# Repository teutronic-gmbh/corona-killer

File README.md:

# Corona-Killer

Luftsterilisation mittels UV-Licht

entworfen für den Einsatz in Klassenräumen im Winterhalbjahr 2020/2021

die eingebaute CO2-Messung erkennt die Anwesenheit von Schülern und schaltet die Luftsterilisation ein

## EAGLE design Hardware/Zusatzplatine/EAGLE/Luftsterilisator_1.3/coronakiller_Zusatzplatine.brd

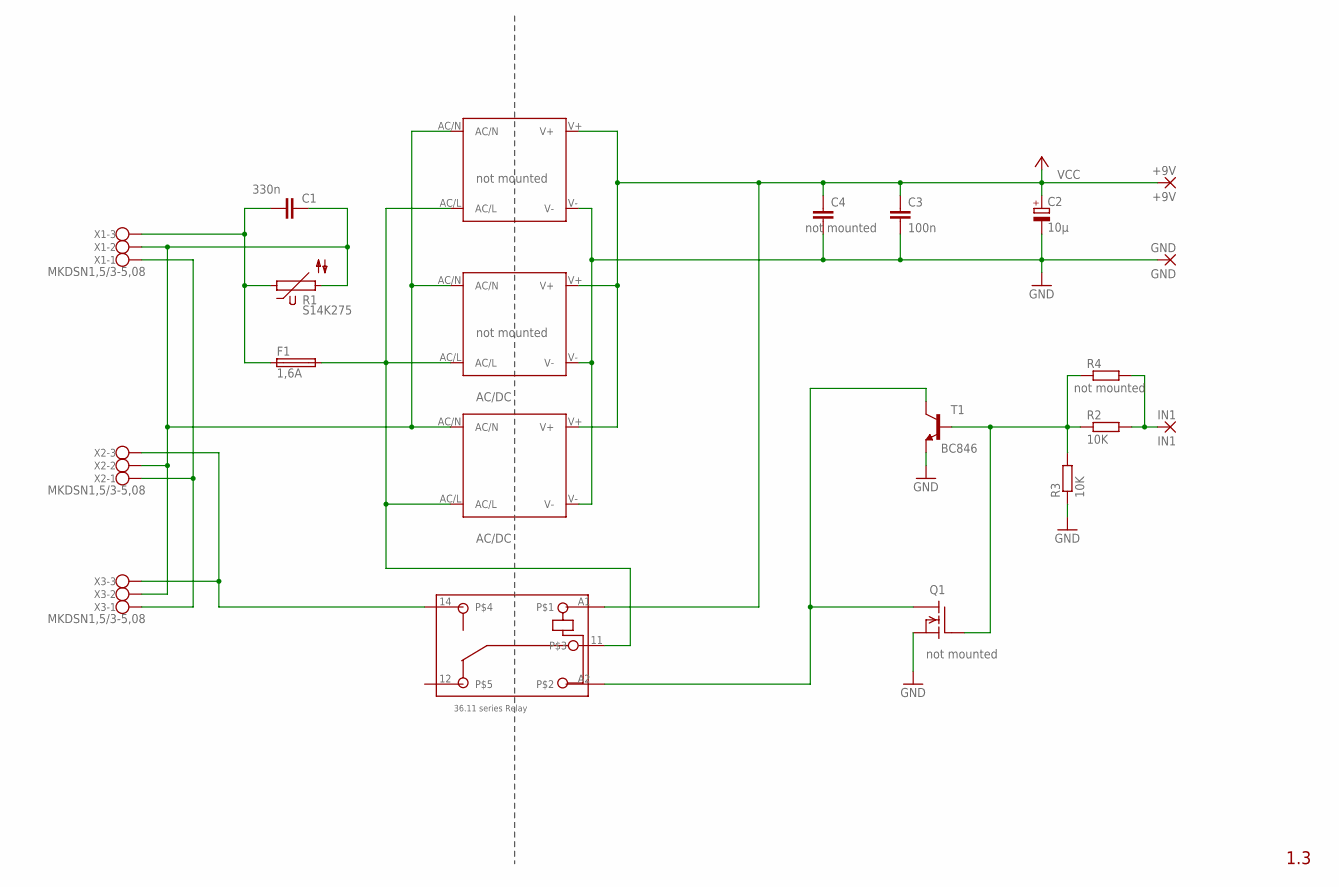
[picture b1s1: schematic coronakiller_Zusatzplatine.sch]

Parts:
+9V: +9V; 2,54/1,0
AC/DC: AC/DC; IRM_03
C1: 330n; C150-054X183
C2: 10µ; E2,5-6
C3: 100n; C0805
C4: not mounted; C025-040X050
F1: 1,6A; SH22,5
GND: GND; 2,54/1,0
IN1: IN1; 2,54/1,0
K1: 36.11
Q1: BSS101; TO92
R1: S14K275
R2, R3: 10K; R0805
R4: not mounted; V526-0
T1: BC846; SOT23
U$1: not mounted; IRM_01/02
U$2: not mounted; IRM_01/02_SMD
X1, X2, X3: MKDSN1,5/3-5,08

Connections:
GND: AC/DC.V-, C2.-, C3.2, C4.2, GND.1, Q1.1 (S), R3.1, T1.2 (E), U$1.V-, U$2.V-
unnamed: C1.2, F1.1, R1.1, X1.3
unnamed: AC/DC.AC/N, C1.1, R1.2, U$1.AC/N, U$2.AC/N, X1.2, X2.2, X3.2
unnamed: X1.1, X2.1, X3.1
unnamed: AC/DC.AC/L, F1.2, K1.11, U$1.AC/L, U$2.AC/L
unnamed: K1.A2, Q1.3 (D), T1.3 (C)
unnamed: Q1.2 (G), R2.1, R3.2, R4.1, T1.1 (B)
unnamed: IN1.1, R2.2, R4.2
unnamed: K1.14, X2.3, X3.3
VCC: +9V.1, AC/DC.V+, C2.+, C3.1, C4.1, K1.A1, U$1.V+, U$2.V+

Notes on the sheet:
1.3
not mounted

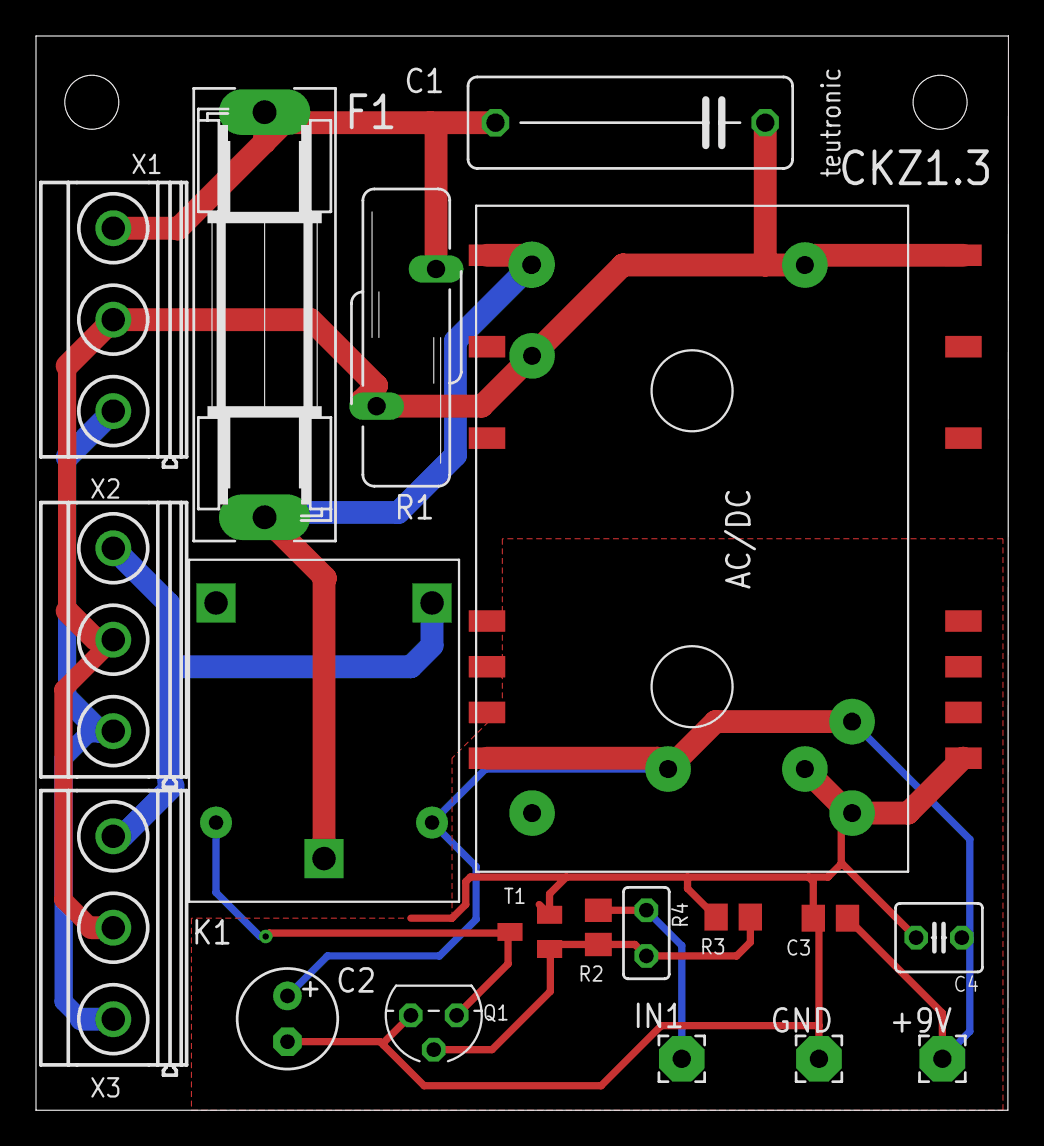
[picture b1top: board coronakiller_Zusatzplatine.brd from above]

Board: 2 copper layers, 54.0 x 59.7 mm, 21 parts (0 on the bottom side), 10 nets.

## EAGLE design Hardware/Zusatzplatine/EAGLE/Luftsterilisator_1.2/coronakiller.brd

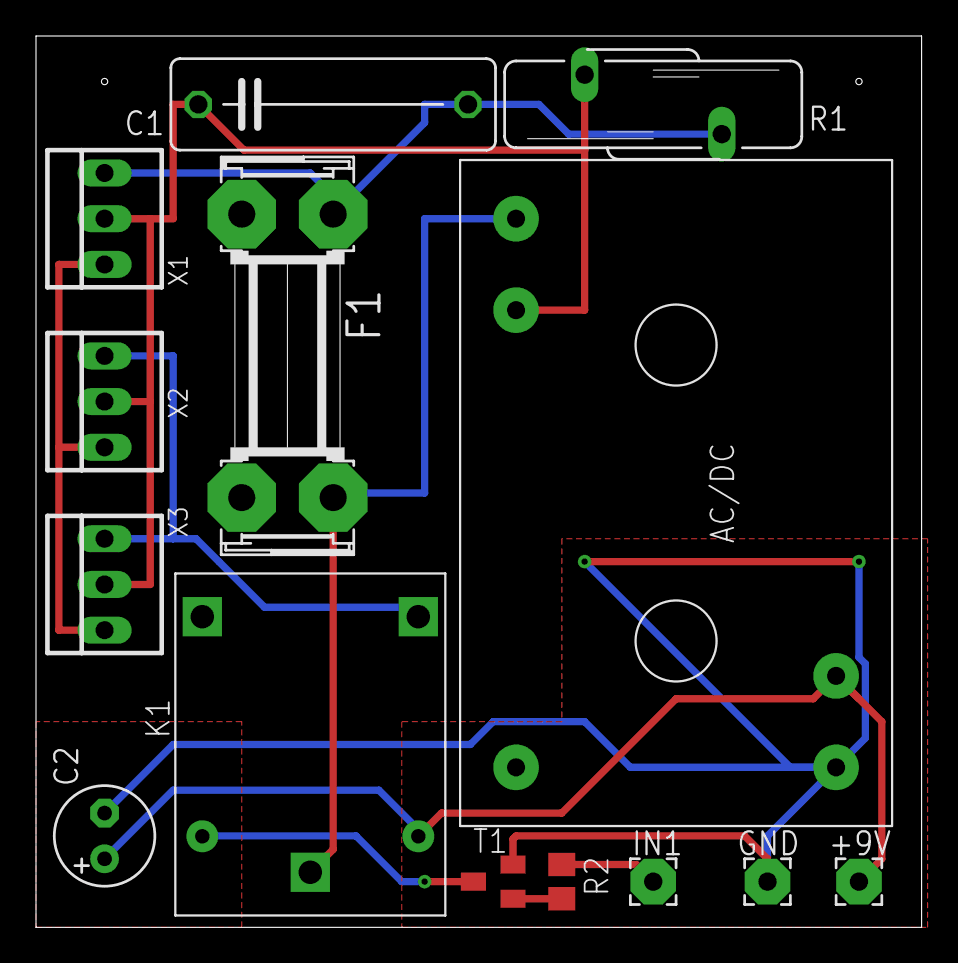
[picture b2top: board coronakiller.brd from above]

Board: 2 copper layers, 49.2 x 49.5 mm, 14 parts (0 on the bottom side), 10 nets.

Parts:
+9V: +9V; 2,54/1,0
AC/DC: AC/DC; IRM_03
C1: 330n; C150-054X183
C2: 10µ; E2,5-6
F1: 1,6A; SHK20Q
GND: GND; 2,54/1,0
IN1: IN1; 2,54/1,0
K1: 36.11
R1: S14K275
R2: 10K; R0805
T1: BC846; SOT23
X1, X2, X3: 22-23-2031

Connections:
GND: AC/DC.V-, C2.-, GND.1, T1.2
unnamed: AC/DC.AC/N, C1.1, R1.2, X1.2, X2.2, X3.2
unnamed: X1.1, X2.1, X3.1
unnamed: C1.2, F1.1A, R1.1, X1.3
unnamed: AC/DC.AC/L, F1.2A, K1.11
unnamed: K1.A2, T1.3
unnamed: R2.1, T1.1
unnamed: IN1.1, R2.2
unnamed: K1.14, X2.3, X3.3
VCC: +9V.1, AC/DC.V+, C2.+, K1.A1

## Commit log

2020-10-25 init readme
2020-10-25 pretested arduino software
2020-10-25 Hardware files , first commit
2020-10-25 hardware PDF and capital S for Software
2020-11-03 Image of the additional board
2020-11-06 add material list
2020-11-06 material list corrected
2020-11-06 added wiring diagram
2020-11-07 more details in wiring diagram
2020-11-09 material list updated
2020-11-10 redesigned EAGLE layout , now version 1.2
2020-11-19 mechanical details ... draft
2020-11-20 update material list
2020-11-26 new hardware version 1.3
